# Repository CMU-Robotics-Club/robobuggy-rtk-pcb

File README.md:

# robobuggy-rtk-pcb
RTK base station PCB

## Layout

- `old-lora-setup/` - KiCad project for the base station radio: Teensy 4.1 + SparkFun LoRa 1W Breakout 915MHz (SPX-18572). Pinout matches `lora_rtcm_broadcast` in [robobuggy-firmware](https://github.com/CMU-Robotics-Club/robobuggy-firmware).
- `library/` — shared project library, registered in the project's `sym-lib-table` / `fp-lib-table` as `robobuggy_rtk` via `${KIPRJMOD}/../library/...`.
  - `robobuggy_rtk.kicad_sym` — `Teensy_4.1`, `SparkFun_LoRa_1W_Breakout_915MHz`
  - `robobuggy_rtk.pretty` — matching footprints (Teensy outer 48 pins; SparkFun breakout headers + 3.3 mm standoff holes)

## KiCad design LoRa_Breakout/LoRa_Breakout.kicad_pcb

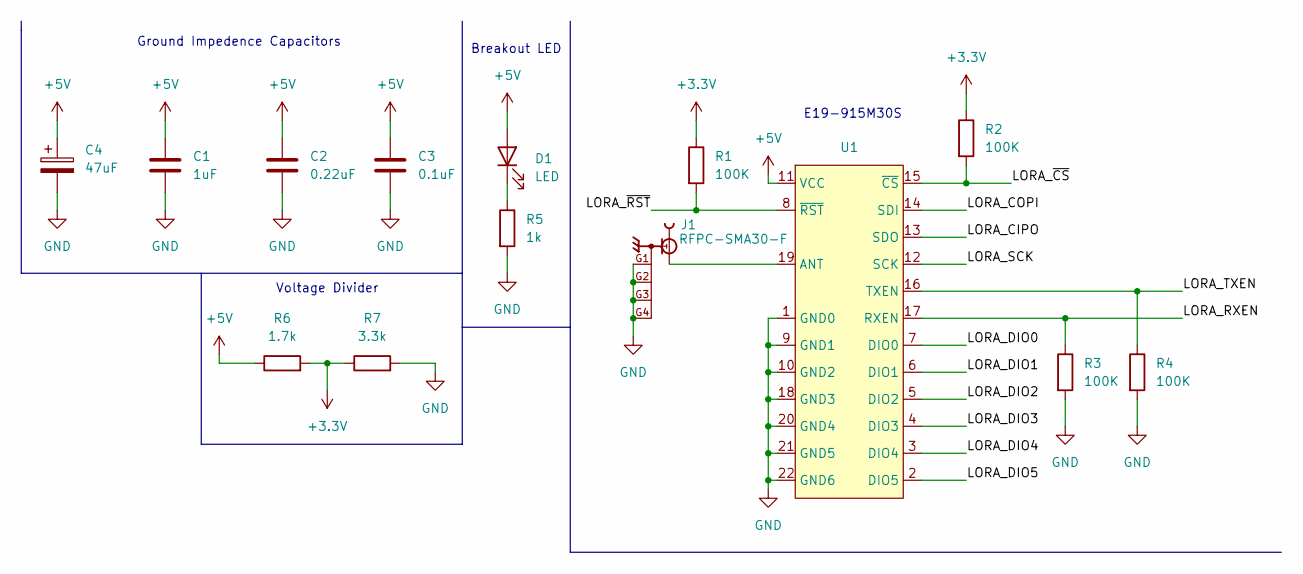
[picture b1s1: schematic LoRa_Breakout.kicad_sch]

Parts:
C1: 1uF; C_0201_0603Metric
C2: 0.22uF; C_0201_0603Metric
C3: 0.1uF; C_0201_0603Metric
C4: 47uF; C_0201_0603Metric
D1: LED; LED_0201_0603Metric
J1: RFPC-SMA30-F; GRADCONN_RFPC-SMA30-F; PARTREV 1.0
R1, R2, R3, R4: 100K; R_0201_0603Metric
R5: 1k; R_0201_0603Metric
R6: 1.7k; R_0201_0603Metric
R7: 3.3k; R_0201_0603Metric
U1: E19-915M30S

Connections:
+3.3V: R1.1, R2.1, R6.2, R7.1
+5V: C1.1, C2.1, C3.1, C4.1, D1.2 (A), R6.1, U1.11 (VCC)
/LORA_CIPO: U1.13 (SDO)
/LORA_COPI: U1.14 (SDI)
/LORA_DIO0: U1.7 (DIO0)
/LORA_DIO1: U1.6 (DIO1)
/LORA_DIO2: U1.5 (DIO2)
/LORA_DIO3: U1.4 (DIO3)
/LORA_DIO4: U1.3 (DIO4)
/LORA_DIO5: U1.2 (DIO5)
/LORA_RXEN: R3.1, U1.17 (RXEN)
/LORA_SCK: U1.12 (SCK)
/LORA_TXEN: R4.1, U1.16 (TXEN)
/LORA_~CS: R2.2, U1.15 (~CS)
/LORA_~RST: R1.2, U1.8 (~RST)
GND: C1.2, C2.2, C3.2, C4.2, J1.G1, J1.G2, J1.G3, J1.G4, R3.2, R4.2, R5.2, R7.2, U1.1 (GND0), U1.9 (GND1), U1.10 (GND2), U1.18 (GND3), U1.20 (GND4), U1.21 (GND5), U1.22 (GND6)
unnamed: D1.1 (K), R5.1
unnamed: J1.1, U1.19 (ANT)

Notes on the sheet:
Breakout LED
E19-915M30S
Voltage Divider
Ground Impedence Capacitors

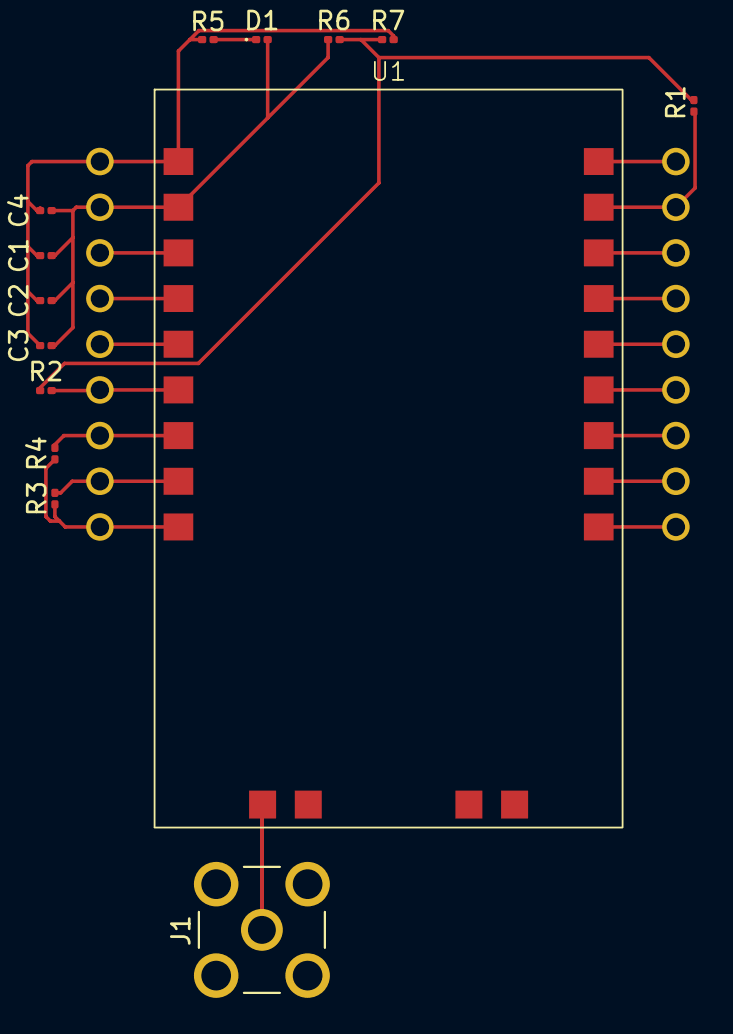
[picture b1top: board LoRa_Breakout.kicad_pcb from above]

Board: 2 copper layers, 14 parts (0 on the bottom side), 9 nets.
